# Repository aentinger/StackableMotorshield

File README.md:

💾 Stackable Motorshield
========================

# 📸 Image

# 📂 Description

The Stackable Motorshield facilitates the control of up to 8 high power motors (18 V / 46 A) using only one Arduino Board. This can be achived by using the same amount of Stackable Motorshields as the amount of motors desired to be controlled. The communication between Motorshields and Arduino Board is done over the I2C-Interface. The address of each Stackable Motorshields can be configured. Inputs for connecting rotary encoders for determining the number of rotations of the motor are available on the shield. For a quick and easy start, a open source Arduino library with sample programs is available.

**Features**

* Control of up to 8 High Power Motors through stacking of up to 8 Stackable Motorshields on top of each other
* Voltage supply range: 7 to 18 Volts
* Can be used with 2S, 3S and 4S LiPo-battery
* High performance: Maximum continuous output 46 A
* Control via I2C -  only 2 Arduino-Pins are required (SDA = A4, SCL = A5)
* I2C-PullUp-resistors connectable through jumper
* Adjustable address through jumper
* Inputs for rotary encoders
* Motor drivers are protected against short circuit (to ground/supply), overheating, overvoltage and undervoltage
* Arduino Library with example programs is available on GitHub
* 2 Status-LEDs (Orange: User LED, Red: Active when speed of motor > 0)

# 🎥 [Video](images/stackable_motorshield_demo.mp4)

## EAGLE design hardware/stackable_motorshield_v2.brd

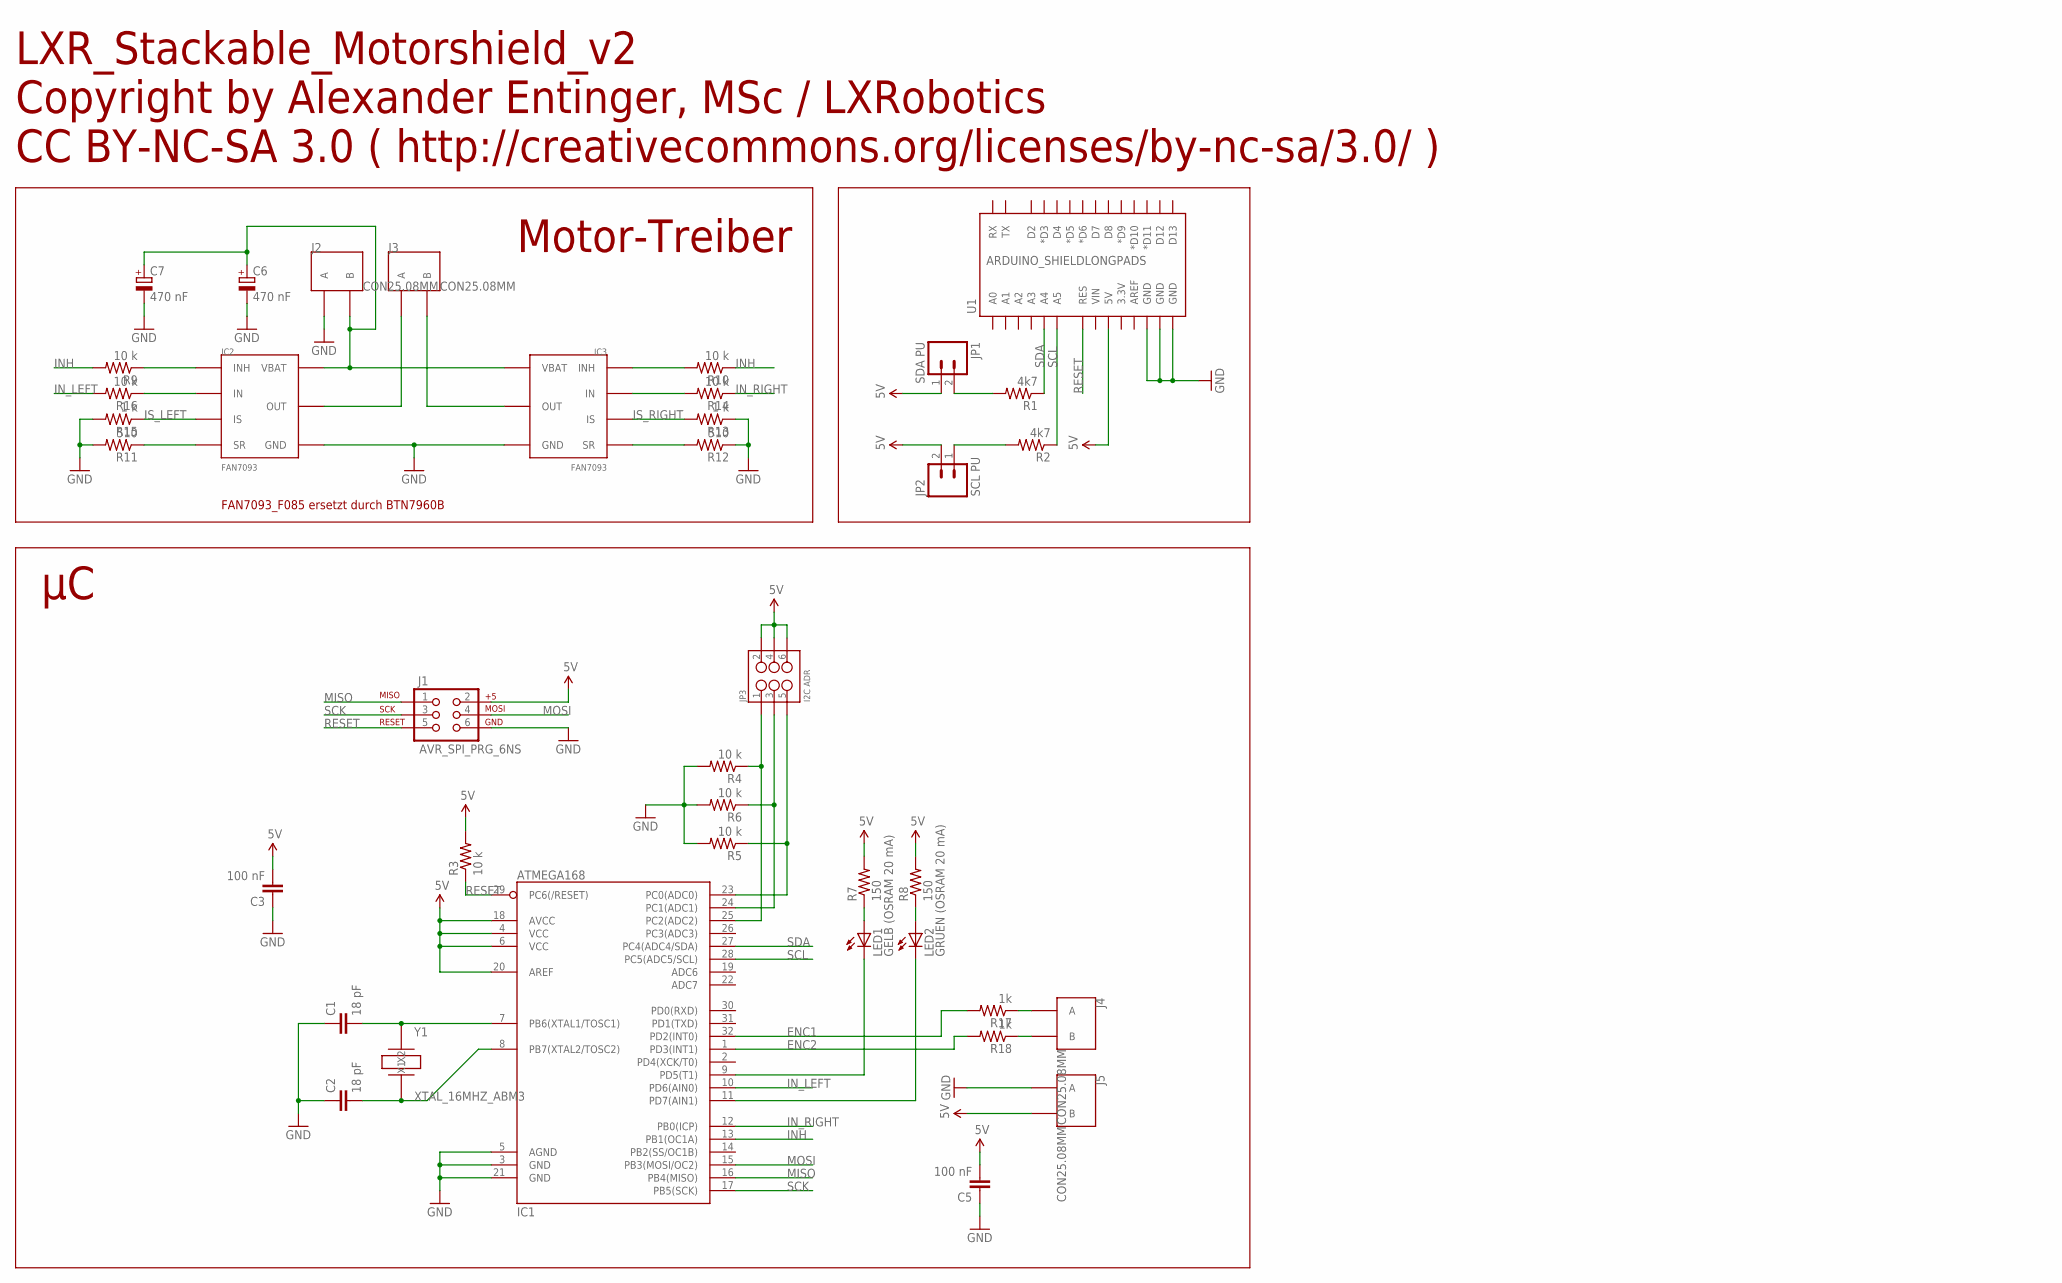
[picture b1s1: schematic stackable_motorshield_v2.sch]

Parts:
C1, C2: 18 pF; C0805
C3, C5: 100 nF; C0805
C6, C7: 470 nF; KEMET_A
IC1: ATMEGA168; TQFP32-08
IC2, IC3: FAN7093; TO263-7L
J1: AVR_SPI_PRG_6NS; 2X3-NS
J2, J3, J4, J5: CON25.08MM; CON2_SCHRAUBKLEMME
JP1: SDA PU; 1X02
JP2: SCL PU; 1X02
JP3: I2C ADR; 2X3_POGO
LED1: GELB (OSRAM 20 mA); CHIP-LED0805
LED2: GRUEN (OSRAM 20 mA); CHIP-LED0805
R1, R2: 4k7; 0805
R3, R4, R5, R6, R9, R10, R14, R16: 10 k; 0805
R7, R8: 150; 0805
R11, R12: 510; 0805
R13, R15: 1 k; 0805
R17, R18: 1k; 0805
U1: ARDUINO_SHIELDLONGPADS; DUEMILANOVE_SHIELD_LONGPADS
Y1: XTAL_16MHZ_ABM3; ABM3

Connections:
5V: C3.2, C5.2, IC1.4 (VCC), IC1.6 (VCC), IC1.18 (AVCC), IC1.20 (AREF), J1.2, J5.2 (B), JP1.1, JP2.2, JP3.P$2 (2), JP3.P$4 (4), JP3.P$6 (6), R3.2, R7.2, R8.2, U1.5V
ENC1: IC1.32 (PD2(INT0)), R17.2
ENC2: IC1.1 (PD3(INT1)), R18.2
GND: C1.1, C2.1, C3.1, C5.1, C6.CATHODE (-), C7.CATHODE (-), IC1.3 (GND), IC1.5 (AGND), IC1.21 (GND), IC2.GND, IC3.GND, J1.6, J2.1 (A), J5.1 (A), R4.2, R5.2, R6.2, R11.2, R12.1, R13.1, R15.2, U1.GND@0 (GND), U1.GND@1 (GND), U1.GND@2 (GND)
INH: IC1.13 (PB1(OC1A)), R9.2, R10.1
IN_LEFT: IC1.10 (PD6(AIN0)), R16.2
IN_RIGHT: IC1.12 (PB0(ICP)), R14.1
IS_LEFT: IC2.IS, R15.1
IS_RIGHT: IC3.IS, R13.2
MISO: IC1.16 (PB4(MISO)), J1.1
MOSI: IC1.15 (PB3(MOSI/OC2)), J1.4
unnamed: C1.2, IC1.7 (PB6(XTAL1/TOSC1)), Y1.X1
unnamed: C2.2, IC1.8 (PB7(XTAL2/TOSC2)), Y1.X2
unnamed: JP2.1, R2.2
unnamed: JP1.2, R1.2
unnamed: IC1.25 (PC2(ADC2)), JP3.P$1 (1), R4.1
unnamed: IC1.24 (PC1(ADC1)), JP3.P$3 (3), R6.1
unnamed: IC1.23 (PC0(ADC0)), JP3.P$5 (5), R5.1
unnamed: IC1.9 (PD5(T1)), LED1.C
unnamed: IC1.11 (PD7(AIN1)), LED2.C
unnamed: LED2.A, R8.1
unnamed: LED1.A, R7.1
unnamed: IC2.SR, R11.1
unnamed: IC3.SR, R12.2
unnamed: IC2.OUT, IC2.OUT@1 (OUT), J3.1 (A)
unnamed: IC2.INH, R9.1
unnamed: IC3.OUT, IC3.OUT@1 (OUT), J3.2 (B)
unnamed: C6.ANODE (+), C7.ANODE (+), IC2.VBATT (VBAT), IC3.VBATT (VBAT), J2.2 (B)
unnamed: J4.1 (A), R17.1
unnamed: IC3.INH, R10.2
unnamed: J4.2 (B), R18.1
unnamed: IC2.IN, R16.1
unnamed: IC3.IN, R14.2
RESET: IC1.29 (PC6(/RESET)), J1.5, R3.1, U1.RES
SCK: IC1.17 (PB5(SCK)), J1.3
SCL: IC1.28 (PC5(ADC5/SCL)), R2.1, U1.A5
SDA: IC1.27 (PC4(ADC4/SDA)), R1.1, U1.A4

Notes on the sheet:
LXR_Stackable_Motorshield_v2 Copyright by Alexander Entinger, MSc / LXRobotics CC BY-NC-SA 3.0 ( http://creativecommons.org/licenses/by-nc-sa/3.0/ )
Motor-Treiber
FAN7093_F085 ersetzt durch BTN7960B

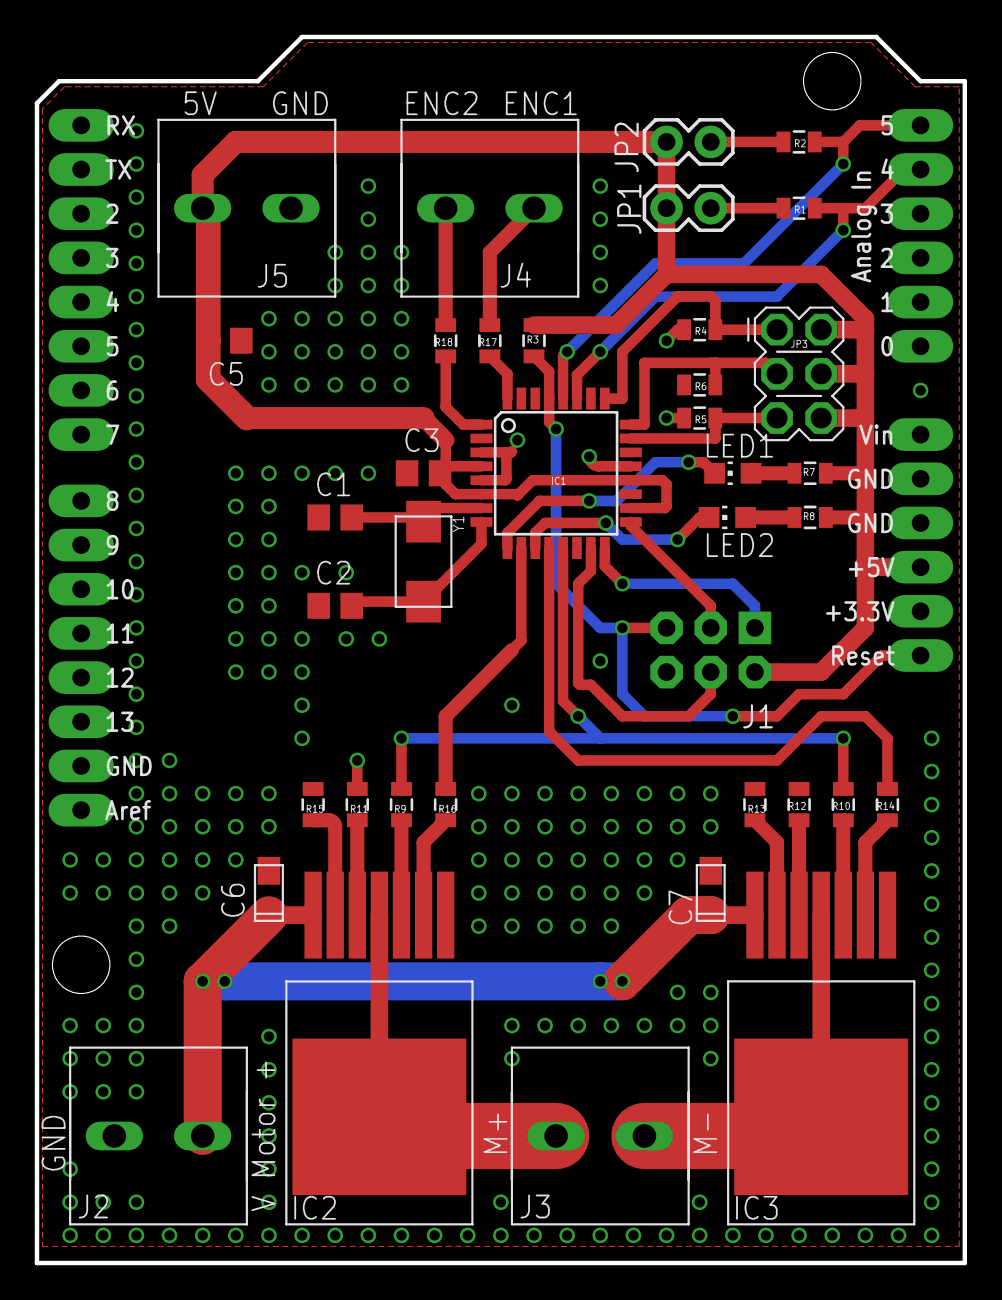
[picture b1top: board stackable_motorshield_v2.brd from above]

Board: 2 copper layers, 53.3 x 70.5 mm, 39 parts (0 on the bottom side), 37 nets.

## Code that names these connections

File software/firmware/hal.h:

/**
 * @author Alexander Entinger, MSc
 * @brief hardware abstraction layer file 
 * @file hal.h
 * @license Attribution-NonCommercial-ShareAlike 3.0 Unported (CC BY-NC-SA 3.0) ( http://creativecommons.org/licenses/by-nc-sa/3.0/ )
 */

#ifndef HAL_H_
#define HAL_H_

#include <avr/io.h>
#include <avr/portpins.h>

// output ports
#define INH_DDR			(DDRB)
#define INH_PORT		(PORTB)
#define INH				(1)

#define INLEFT_DDR		(DDRD)
#define INLEFT_PORT		(PORTD)
#define INLEFT			(6)

#define INRIGHT_DDR		(DDRB)
#define INRIGHT_PORT	(PORTB)
#define INRIGHT			(0)

#define LED_RED_DDR		(DDRD)
#define LED_RED_PORT	(PORTD)
#define LED_RED			(7)

#define LED_ORANGE_DDR	(DDRD)
#define LED_ORANGE_PORT	(PORTD)
#define LED_ORANGE		(5)

// input ports
#define ENC1_DDR		(DDRD)
#define ENC1_PORT		(PORTD)
#define ENC1			(2)

#define ENC2_DDR		(DDRD)
#define ENC2_PORT		(PORTD)
#define ENC2			(3)

#define I2C_ADR_BIT_0_DDR	(DDRC)
#define I2C_ADR_BIT_0_PORT	(PORTC)
#define I2C_ADR_BIT_0_PIN	(PINC)
#define I2C_ADR_BIT_0		(0)

#define I2C_ADR_BIT_1_DDR	(DDRC)
#define I2C_ADR_BIT_1_PORT	(PORTC)
#define I2C_ADR_BIT_1_PIN	(PINC)
#define I2C_ADR_BIT_1		(1)

#define I2C_ADR_BIT_2_DDR	(DDRC)
#define I2C_ADR_BIT_2_PORT	(PORTC)
#define I2C_ADR_BIT_2_PIN	(PINC)
#define I2C_ADR_BIT_2		(2)


#endif /* HAL_H_ */

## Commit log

2013-11-28 changed readme
2014-01-15 initial checkin of stackable motorshield
2014-08-20 adding new schematic - FAN7093 replaced with BTN7960B
2014-08-20 updated v2.png
2014-10-31 adding binary for stackable motorshield onboard µC
2017-06-26 Adding hardware files + images
2025-03-26 Add BOM.
2025-03-26 Add demo video.
2025-03-26 Pretty up README.

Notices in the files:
README.md:
License: CC BY-NC-SA 4.0
parts and their libraries:
SparkFun-Boards: Licensing: CC v3.0 Share-Alike You are welcome to use this library for commercial purposes.
